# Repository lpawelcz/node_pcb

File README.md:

ESP32 - measurement node board design

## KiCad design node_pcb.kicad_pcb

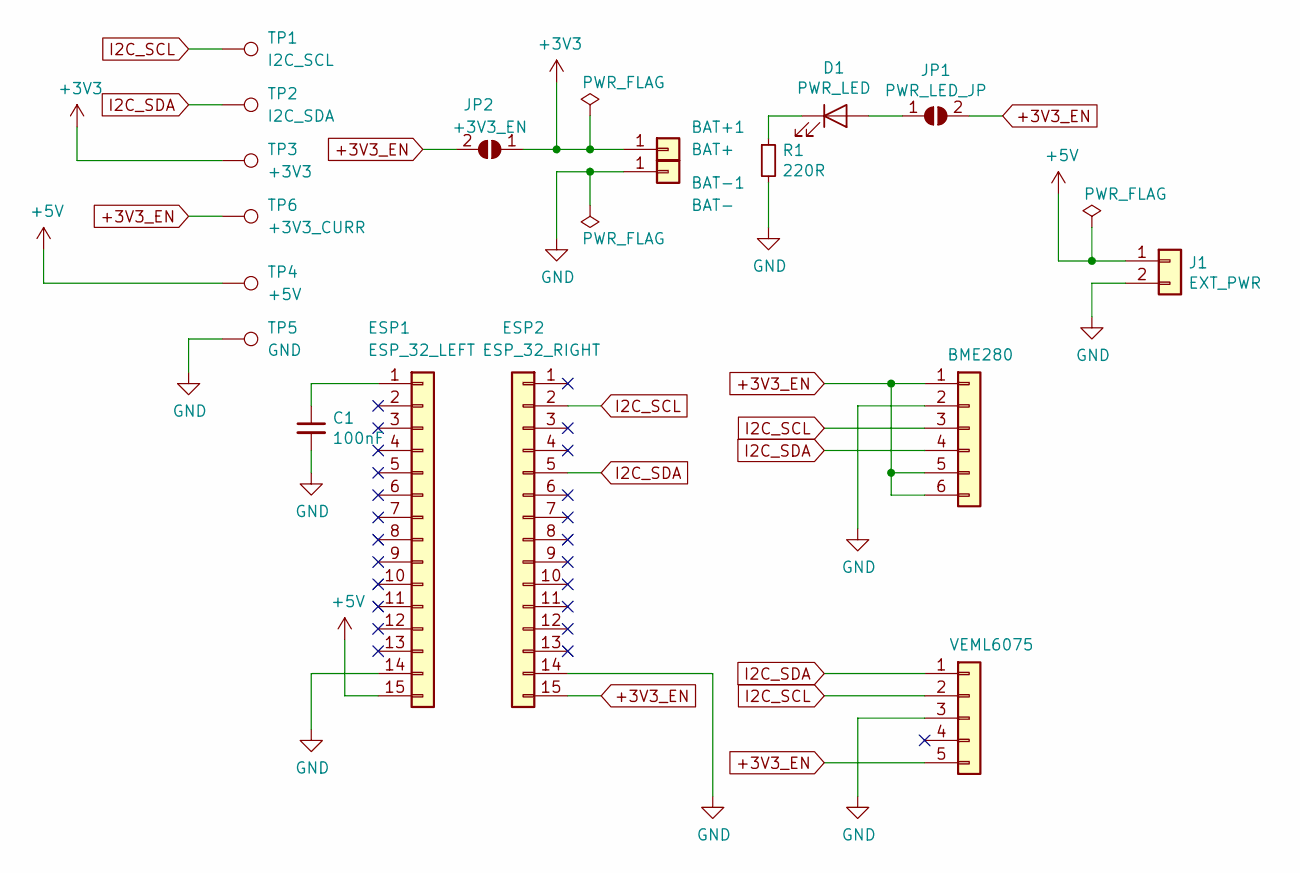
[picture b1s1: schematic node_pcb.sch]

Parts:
BAT+1: BAT+; TestPoint_THTPad_D1.5mm_Drill0.7mm
BAT-1: BAT-; TestPoint_THTPad_D1.5mm_Drill0.7mm
BME280: Conn_01x06; PinSocket_1x06_P2.54mm_Vertical
C1: 100nF; C_0805_2012Metric_Pad1.15x1.40mm_HandSolder
D1: PWR_LED; D_0805_2012Metric_Pad1.15x1.40mm_HandSolder
ESP1: ESP_32_LEFT; PinSocket_1x15_P2.54mm_Vertical
ESP2: ESP_32_RIGHT; PinSocket_1x15_P2.54mm_Vertical
J1: EXT_PWR; PinHeader_1x02_P2.54mm_Horizontal
JP1: PWR_LED_JP; SolderJumper-2_P1.3mm_Open_RoundedPad1.0x1.5mm
JP2: +3V3_EN; SolderJumper-2_P1.3mm_Open_RoundedPad1.0x1.5mm
R1: 220R; R_0805_2012Metric_Pad1.15x1.40mm_HandSolder
TP1: I2C_SCL; TestPoint_Bridge_Pitch2.0mm_Drill0.7mm
TP2: I2C_SDA; TestPoint_Bridge_Pitch2.0mm_Drill0.7mm
TP3: +3V3; TestPoint_Bridge_Pitch2.0mm_Drill0.7mm
TP4: +5V; TestPoint_Bridge_Pitch2.0mm_Drill0.7mm
TP5: GND; TestPoint_Bridge_Pitch2.0mm_Drill0.7mm
TP6: +3V3_CURR; TestPoint_Bridge_Pitch2.0mm_Drill0.7mm
VEML6075: Conn_01x05; PinSocket_1x05_P2.54mm_Vertical

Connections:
+3V3: BAT+1.1, JP2.1 (A), TP3.1
+3V3_EN: BME280.1, BME280.5, BME280.6, ESP2.15, JP1.2 (B), JP2.2 (B), TP6.1, VEML6075.5
+5V: ESP1.15, J1.1, TP4.1
GND: BAT-1.1, BME280.2, C1.2, ESP1.14, ESP2.14, J1.2, R1.2, TP5.1, VEML6075.3
I2C_SCL: BME280.3, ESP2.2, TP1.1, VEML6075.2
I2C_SDA: BME280.4, ESP2.5, TP2.1, VEML6075.1
unnamed: C1.1, ESP1.1
unnamed: D1.1 (K), R1.1
unnamed: D1.2 (A), JP1.1 (A)

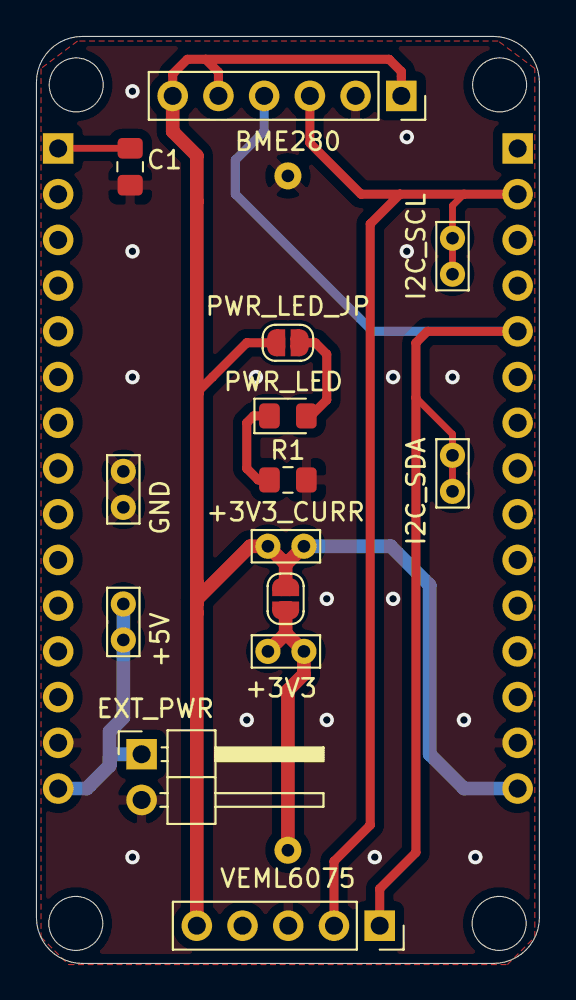
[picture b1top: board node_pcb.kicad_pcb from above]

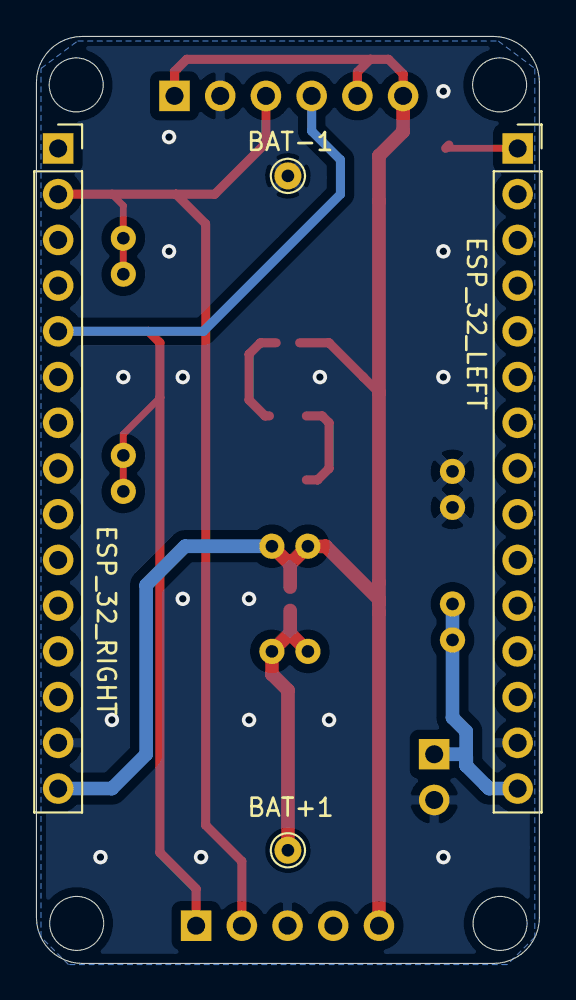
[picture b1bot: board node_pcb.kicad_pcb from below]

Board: 2 copper layers, 27.9 x 51.5 mm, 18 parts (4 on the bottom side), 9 nets.

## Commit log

2019-11-19 ESP32 - measurement node board design
2019-11-19 add readme
2019-11-20 dimensions fix
2019-11-20 bigger dimensions
2019-11-21 pictures update
